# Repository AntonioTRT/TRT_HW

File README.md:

# TRT_HW
# STM32 Modular Audio Platform

Plataforma de hardware abierta en arquitectura Tarjeta Base y Hijas (Carrier & Daughterboard) para audio digital, DSP y control.

## Especificaciones
* MCU: STM32G474RET6 (Cortex-M4 @ 170MHz)
* Aceleradores: FMAC y CORDIC
* Bus B2B: I2S, I2C, SPI, ADC, GPIO
* Alimentación: USB-C / 9V DC
* ECAD: KiCad

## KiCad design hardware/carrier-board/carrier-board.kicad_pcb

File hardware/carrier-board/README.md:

# STM32G474RET6 Carrier Board — Especificación Técnica Oficial

## 1. Descripción General

La **Carrier Board STM32G474** es una plataforma de desarrollo modular de alto rendimiento basada en el microcontrolador ARM Cortex-M4F **STM32G474RET6** (LQFP-64, hasta 170 MHz con FPU y DSP). Diseñada específicamente para fabricación y ensamblaje SMT en **JLCPCB**, utiliza encapsulados estándar fáciles de inspeccionar y soldar (**0805 pasivos, SOT-23, SOD-123 y LQFP-64**).

La tarjeta se interconecta con placas hijas (*daughterboards*) a través del conector Board-to-Board principal **J2 (2x8 pines, numeración estándar 1 a 16)**, integrando buses de comunicación (SPI1, I2C1 con gestión de energía), control de potencia (driver de motor PWM con MOSFET AO3400A) e identificación de hardware digital (HWID de 4 bits).

---

## 2. Especificaciones de Hardware

### 2.1. Alimentación y Regulación
- **Entrada Principal:** +5V nominal vía puerto **USB-C (J6)**. Cuenta con resistencias de pull-down de **5.1 kΩ** en las líneas `CC1` y `CC2` para compatibilidad completa con fuentes y cables USB-C a USB-C (Power Delivery Sink 5V/3A máx).
- **Regulador LDO:** **AMS1117-3.3** en encapsulado SOT-223, entregando un riel de +3.3V regulado (hasta 800 mA de pico / 1 A máx).
- **Filtrado y Desacoplo:**
  - Capacitores cerámicos (MLCC 0805) de **10 µF** en la entrada (+5V) y salida (+3.3V) del regulador.
  - Red de desacoplo distribuida en el MCU: **100 nF** en cada par `VDD`/`VSS` adyacente a los pines, complementados por un capacitor de carga de **10 µF**.
  - **Filtro Analógico:** Perla de ferrita (**FB1**) con capacitor de **100 nF** a masa para las líneas `VDDA` y `VREF+`, aislando el dominio analógico de ruidos digitales.
  - Pin `VBAT` unificado directamente al riel de **+3.3V**.

### 2.2. Reloj, Reset y Depuración
- **Oscilador Principal (HSE):** Cristal de cuarzo pasivo de **8.000 MHz** con capacitores de carga de **22 pF** a GND en `OSC_IN` (PF0) y `OSC_OUT` (PF1).
- **Circuito de Reset (NRST):** Pulsador táctil a GND con resistencia de pull-up de **10 kΩ** a +3.3V y capacitor cerámico de **100 nF** para supresión de rebotes mecánicos y transitorios.
- **Depuración SWD:** Huella estándar **Tag-Connect TC2030-NL / TC2030** que provee:
  - `SWDIO` en **PA13**
  - `SWCLK` en **PA14**
  - `SWO` en **PB3** (Asynchronous Trace)
  - `NRST` para hardware reset por depurador
  - `+3.3V` (VTref) y `GND`

### 2.3. Periféricos e Interfaces On-Board
- **Bus I2C1 con Gestión de Energía:**
  - `PB9` (SDA) y `PB8` (SCL).
  - Resistencias de Pull-Up de **2.2 kΩ** conectadas a un nodo conmutable controlado por el pin **PC15** (`I2C_PU_EN`).
  - Permite desconectar los pull-ups para apagar el bus en modos de bajo consumo (*Sleep/Stop*).
- **Bus SPI1:**
  - `PA5` (SCK), `PA6` (MISO), `PA7` (MOSI), `PB6` (CS).
- **Driver de Motor Low-Side (PWM):**
  - MOSFET canal N **AO3400A** (30V, 5.7A, $R_{DS(on)} < 35\text{ m}\Omega$ a 3.3V $V_{GS}$) en encapsulado SOT-23.
  - Controlado desde el pin **PB4** (Timer 3, Canal 1 / `TIM3_CH1`).
  - Red de compuerta: Resistencia de gate $R_G = 100\ \Omega$ y resistencia pull-down de seguridad $R_{PD} = 10\text{ k}\Omega$ a GND.
  - Protección inductiva: Diodo Schottky Flyback **1N5819HW** (SOD-123) en antiparalelo con la carga + capacitor cerámico de **100 nF** para amortiguación de EMI.
  - Conector de salida de motor **J1** (Paso 2.54 mm): Pin 1 = `+5V`, Pin 2 = `Drain del MOSFET`.
- **LEDs de Diagnóstico:**
  - `LED_PWR` (Verde): Polarizado a +3.3V mediante resistencia de **1 kΩ** ($I_F \approx 1.3\text{ mA}$).
  - `LED_USER` (Azul): Conectado al pin **PA5** (`SPI_SCK`) mediante resistencia de **470 Ω** (emula el `LED_BUILTIN` de Arduino Pin 13).

---

## 3. Conector Board-to-Board (J2 — 2x8 Pines, Numeración Estándar 1 a 16)

El conector principal **J2** utiliza una huella estándar de doble hilera (paso 2.00 mm / 2.54 mm) con numeración numérica consecutiva (Pines 1 al 16), organizada en fila impar (señales SPI / HWID) y fila par (alimentación / I2C / GPIOs):

### 3.1. Tabla de Mapeo Definitiva para J2

| Pin Físico J2 | Fila | Etiqueta de Red | Pin STM32G474 | Funciones Nativas STM32 | Equivalente Arduino | Descripción |
| :---: | :---: | :--- | :---: | :--- | :---: | :--- |
| **Pin 1** | Impar | `SPI_CS / PWM` | **PB6** | TIM4_CH1, TIM16_CH1N, USART1_TX | D10 / PWM | Chip Select SPI o PWM auxiliar |
| **Pin 2** | Par | `GND` | — | Riel de Masa común (0V) | GND | Masa de alimentación |
| **Pin 3** | Impar | `SPI_MOSI / PWM`| **PA7** | SPI1_MOSI, TIM3_CH2, TIM1_CH1N | D11 / PWM | Datos MOSI o salida PWM |
| **Pin 4** | Par | `+5V` | — | Riel de entrada USB VBUS | 5V | Alimentación de potencia principal |
| **Pin 5** | Impar | `SPI_MISO / PWM`| **PA6** | SPI1_MISO, TIM3_CH1, TIM16_CH1, ADC2_IN3 | D12 / PWM | Datos MISO o entrada ADC / PWM |
| **Pin 6** | Par | `TRT_GPIO_1` | **PA1** | TIM2_CH2, USART2_RTS, ADC1_IN2 | D2 / A4 | GPIO / Entrada Analógica / Timer |
| **Pin 7** | Impar | `SPI_SCK / PWM` | **PA5** | SPI1_SCK, TIM2_CH1, ADC2_IN2 | D13 / SCK | Reloj SPI / LED Builtin / PWM |
| **Pin 8** | Par | `+3.3V` | — | Salida del LDO AMS1117-3.3 | 3.3V | Lógica y alimentación de sensores |
| **Pin 9** | Impar | `HWID_0` | **PC0** | ADC1_IN6, ADC2_IN6, LPTIM1_IN1 | A0 | Identificación Hardware Bit 0 (ADC/Digital) |
| **Pin 10**| Par | `TRT_GPIO_2` | **PA4** | DAC1_OUT1, SPI1_NSS, ADC2_IN1 | A5 / DAC | GPIO / Salida Analógica Pura DAC |
| **Pin 11**| Impar | `HWID_1` | **PC1** | ADC1_IN7, ADC2_IN7, LPTIM1_OUT | A1 | Identificación Hardware Bit 1 (ADC/Digital) |
| **Pin 12**| Par | `SDA` | **PB9** | I2C1_SDA, TIM4_CH4, FDCAN1_TX | D14 / SDA | Datos I2C1 (Pull-up conmutable vía PC15) |
| **Pin 13**| Impar | `HWID_2` | **PC2** | ADC1_IN8, ADC2_IN8, LPTIM1_IN2 | A2 | Identificación Hardware Bit 2 (ADC/Digital) |
| **Pin 14**| Par | `SCL` | **PB8** | I2C1_SCL, TIM4_CH3, FDCAN1_RX | D15 / SCL | Reloj I2C1 (Compartido con BOOT0) |
| **Pin 15**| Impar | `HWID_3` | **PC3** | ADC1_IN9, ADC2_IN9, LPTIM1_ETR | A3 | Identificación Hardware Bit 3 (ADC/Digital) |
| **Pin 16**| Par | `TRT_GPIO_3` | **PB0** | TIM1_CH2N, TIM3_CH3, ADC1_IN15 | D3 / PWM | GPIO / PWM auxiliar / ADC |

---

### 3.2. Distribución Física de Pines en el Header (Vista Superior)

```text
               +-------------------+
SPI_CS   (PB6) | [ 1]         [ 2] | GND
SPI_MOSI (PA7) | [ 3]         [ 4] | +5V
SPI_MISO (PA6) | [ 5]         [ 6] | TRT_GPIO_1 (PA1)
SPI_SCK  (PA5) | [ 7]         [ 8] | +3.3V
HWID_0   (PC0) | [ 9]         [10] | TRT_GPIO_2 (PA4)
HWID_1   (PC1) | [11]         [12] | SDA        (PB9)
HWID_2   (PC2) | [13]         [14] | SCL        (PB8)
HWID_3   (PC3) | [15]         [16] | TRT_GPIO_3 (PB0)
               +-------------------+
                    Conector J2
```

---

## 4. Pines Internos y Periféricos Dedicados

| Función | Pin STM32G474 | Características |
| :--- | :--- | :--- |
| **Driver Motor (GATE)** | **PB4** | TIM3_CH1 (PWM Low-Side, MOSFET AO3400A a conector J1) |
| **Habilitador Pull-Up I2C**| **PC15** | Control digital de polarización para resistencias I2C1 (Push-Pull HIGH = ON, High-Z = OFF) |
| **LED Usuario (Azul)** | **PA5** | Compartido con SPI1_SCK (R=470Ω a GND) |
| **USB D-** | **PA11** | USB 2.0 Full Speed Data - |
| **USB D+** | **PA12** | USB 2.0 Full Speed Data + |
| **SWDIO** | **PA13** | Tag-Connect Pin 4 |
| **SWCLK** | **PA14** | Tag-Connect Pin 2 |
| **SWO** | **PB3** | Tag-Connect Pin 6 (Asynchronous SWO Trace) |

---

## 5. Guía de Integración de Firmware

### 5.1. Configuración de Option Bytes para PB8 / BOOT0
El microcontrolador **STM32G474RET6** multiplexa el pin físico 60 entre `PB8` y la señal de selección de arranque `BOOT0`.
- **Problema:** De fábrica, si `nBOOT0_SEL = 1`, en cada reinicio el hardware muestrea el pin PB8. Dado que PB8 está conectado a la línea I2C `SCL` con una resistencia de pull-up, el MCU detectará un nivel alto (`BOOT0 = 1`) y entrará en el bootloader DFU de ST en lugar de ejecutar la memoria Flash.
- **Solución Obligatoria:** Configurar el registro de Option Bytes `FLASH_OPTR`:
  - `nBOOT0_SEL = 0` (Bit 27): El valor de BOOT0 es ignorado desde el pin físico PB8 y se toma del bit de software `nBOOT0`.
  - `nBOOT0 = 1` (Bit 26): En lógica invertida, un valor de `1` equivale a `BOOT0 = 0`, forzando el arranque directo desde la **Flash Principal**.

#### Configuración por Software (HAL / Firmware):
```c
void Configure_Boot_OptionBytes(void) {
    FLASH_OBProgramInitTypeDef obInit = {0};
    
    HAL_FLASH_Unlock();
    HAL_FLASH_OB_Unlock();

    HAL_FLASHEx_OBGetConfig(&obInit);
    
    // Si nBOOT0_SEL está en 1 (muestreo por pin físico PB8), cambiar a software
    if ((obInit.UserConfig & FLASH_OPTR_nBOOT0_SEL) != 0) {
        obInit.OptionType = OPTIONBYTE_USER;
        obInit.UserType   = OB_USER_nBOOT0_SEL | OB_USER_nBOOT0;
        // nBOOT0_SEL = 0 (software), nBOOT0 = 1 (arranque en Flash)
        obInit.UserConfig = OB_nBOOT0_SEL_DISABLE | OB_nBOOT0_SET;
        
        HAL_FLASHEx_OBProgram(&obInit);
        HAL_FLASH_OB_Launch(); // Aplica cambios y reinicia el MCU
    }

    HAL_FLASH_OB_Lock();
    HAL_FLASH_Lock();
}
```

---

### 5.2. Control de Pull-Ups I2C vía PC15 (`I2C_PU_EN`)
Las resistencias de 2.2 kΩ están conectadas al pin **PC15**.

> [!WARNING]
> **Regla de Oro de Firmware para PC15:**
> - Para **ACTIVAR** el bus I2C: Configurar `PC15` como **Salida Push-Pull** en nivel **ALTO** (`GPIO_PIN_SET` = 3.3V).
> - Para **DESACTIVAR** el bus I2C: Configurar `PC15` como **Entrada Flotante (High-Z / No-Pull)**.
> - **NUNCA** configurar `PC15` como salida en nivel **BAJO** (`0V`), ya que esto forzaría a masa las líneas `SDA` y `SCL` mediante 2.2 kΩ, bloqueando la comunicación y consumiendo corriente innecesaria.

#### Implementación HAL:
```c
// Activa las resistencias de pull-up (Bus I2C operativo)
void I2C_Pullups_Enable(void) {
    GPIO_InitTypeDef GPIO_InitStruct = {0};
    __HAL_RCC_GPIOC_CLK_ENABLE();

    GPIO_InitStruct.Pin = GPIO_PIN_15;
    GPIO_InitStruct.Mode = GPIO_MODE_OUTPUT_PP;
    GPIO_InitStruct.Pull = GPIO_NOPULL;
    GPIO_InitStruct.Speed = GPIO_SPEED_FREQ_LOW;
    HAL_GPIO_Init(GPIOC, &GPIO_InitStruct);

    HAL_GPIO_WritePin(GPIOC, GPIO_PIN_15, GPIO_PIN_SET); // Alimenta +3.3V al nodo
}

// Desconecta las resistencias de pull-up (Modo bajo consumo)
void I2C_Pullups_Disable(void) {
    GPIO_InitTypeDef GPIO_InitStruct = {0};
    __HAL_RCC_GPIOC_CLK_ENABLE();

    // Configurar en entrada de alta impedancia (High-Z)
    GPIO_InitStruct.Pin = GPIO_PIN_15;
    GPIO_InitStruct.Mode = GPIO_MODE_INPUT;
    GPIO_InitStruct.Pull = GPIO_NOPULL;
    HAL_GPIO_Init(GPIOC, &GPIO_InitStruct);
}
```

---

### 5.3. Control del Driver de Motor PWM (PB4 / TIM3_CH1)
El MOSFET **AO3400A** es activado directamente por lógica de 3.3V desde `PB4`.

- **Frecuencia óptima recomendada:** 10 kHz a 20 kHz.
- Reloj APB1 (`TIM3CLK`) = 170 MHz.
  - `Prescaler = 16` $\rightarrow$ Frecuencia de conteo = 10 MHz.
  - `Period (ARR) = 999` $\rightarrow$ Frecuencia PWM = 10 kHz ($10\text{ MHz} / 1000$).
  - Resolución del ciclo de trabajo: 0 a 1000 (0% a 100%).

```c
// Iniciar señal PWM
HAL_TIM_PWM_Start(&htim3, TIM_CHANNEL_1);

// Modificar velocidad del motor (0 a 1000)
void Motor_SetSpeed(uint16_t speed) {
    if (speed > 1000) speed = 1000;
    __HAL_TIM_SET_COMPARE(&htim3, TIM_CHANNEL_1, speed);
}
```

---

## 6. Checklist Crítico para el Layout de PCB (JLCPCB)

1. **Ruta de Retorno y Bucles de Potencia del Motor (J1 / AO3400A / D1):**
   - El bucle cerrado formado por `J1 Pin 1 (+5V)` $\rightarrow$ `Motor` $\rightarrow$ `J1 Pin 2` $\rightarrow$ `Diodo 1N5819HW` debe colocarse **lo más compacto posible** para minimizar la radiación EMI.
   - Pistas de potencia entre `J1`, el Drain del MOSFET y el Source a `GND` con un ancho mínimo de **1.2 mm a 1.5 mm** (o polígono de cobre).
   - Colocar el Source del MOSFET directamente a la masa general mediante múltiples vías a plano de masa para evitar ruido por rebote de masa (*ground bounce*).
2. **Ubicación de Condensadores de Desacoplo del MCU:**
   - Cada condensador de **100 nF** debe colocarse inmediatamente adyacente a su respectivo pin `VDD`, conectando primero el pad del capacitor antes de la vía hacia el plano interno.
   - La perla de ferrita `FB1` y su capacitor de 100 nF para `VDDA`/`VREF+` deben ubicarse pegados a los pines 18 y 19.
3. **Oscilador de Cristal HSE de 8 MHz (PF0 / PF1):**
   - Trazar pistas cortas y simétricas entre el cristal y los pines del MCU.
   - Colocar un anillo de guarda de masa (`GND guard ring`) alrededor del cristal y sus capacitores de 22 pF.
   - No rutear señales digitales de alta velocidad (como PWM o SPI) por debajo del oscilador.
4. **Par Diferencial USB (PA11 / PA12):**
   - Impedancia diferencial de **90 Ω**. Ruteo en paralelo con separación constante y longitudes simétricas acopladas.
   - Mantener el plano de masa continuo por debajo sin cortes.

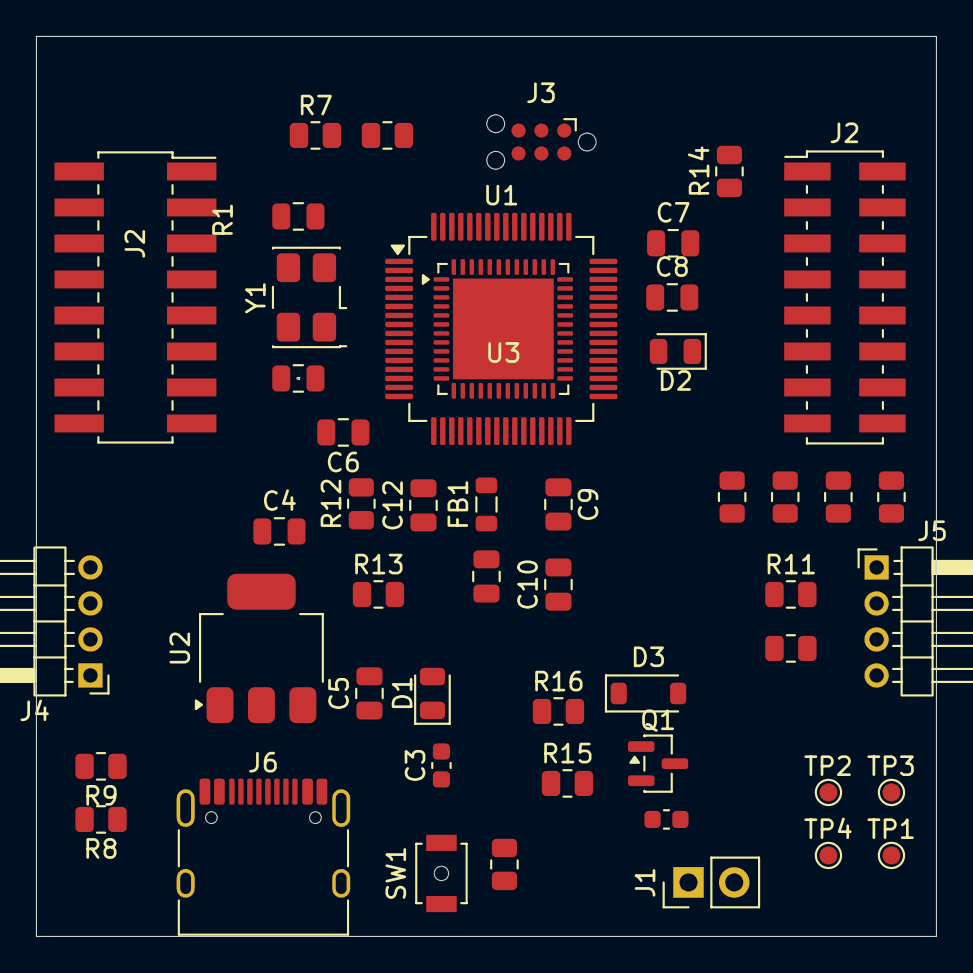
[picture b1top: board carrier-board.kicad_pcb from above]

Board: 4 copper layers, 50.0 x 50.0 mm, 50 parts (0 on the bottom side), 35 nets, no tracks yet.

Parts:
C1, C2: 22pf; C_0805_2012Metric
C3, C13: 100nf; C_0603_1608Metric
C4, C5, C10: 10uF; C_0805_2012Metric
C6, C7, C8, C9, C11, C12: 100nF; C_0805_2012Metric
D1, D2: LED; LED_0805_2012Metric
D3: 1N5819HW; D_SOD-123
FB1: FerriteBead; L_0805_2012Metric
J1: Conn_01x02_Pin; PinHeader_1x02_P2.54mm_Vertical
J2: DIN41612_02x08_AB_EvenPins; PinSocket_2x08_P2.00mm_Vertical_SMD
J2#2: DIN41612_02x08_AB_EvenPins; PinHeader_2x08_P2.00mm_Vertical_SMD
J3: TC2030; Tag-Connect_TC2030-IDC-NL_2x03_P1.27mm_Vertical
J4: Conn_01x04_Socket; PinHeader_1x04_P2.00mm_Horizontal
J5: Conn_01x04_Pin; PinHeader_1x04_P2.00mm_Horizontal
J6: USB_C_Receptacle_USB2.0_16P; USB_C_Receptacle_HRO_TYPE-C-31-M-12
Q1: AO3400A; SOT-23
R1, R2, R3, R4, R5, R6, R7, R12, R15: 10k; R_0805_2012Metric
R8, R9: 5.1k; R_0805_2012Metric
R10, R11: 2.2K; R_0805_2012Metric
R13: 1k; R_0805_2012Metric
R14: 470; R_0805_2012Metric
R16: 100; R_0805_2012Metric
SW1: SW_Push; SW_SPST_B3U-1000P-B
TP1, TP2, TP3, TP4: TestPoint; TestPoint_Pad_D1.0mm
U1: STM32G474RETx; LQFP-64_10x10mm_P0.5mm
U2: AMS1117-3.3; SOT-223-3_TabPin2
U3: STM32F411CEUx; QFN-48-1EP_7x7mm_P0.5mm_EP5.6x5.6mm
Y1: Crystal_GND3; Crystal_SMD_5032-4Pin_5.0x3.2mm

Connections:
+3.3V: C4.1, C6.1, C7.1, C8.1, C9.1, C10.1, FB1.1, J2#2.8, J3.1, R1.1, R7.1, R13.1, TP1.1 (1_1), TP3.1 (1_1), U1.1 (VBAT), U1.16 (VDD), U1.28 (VREF+), U1.32 (VDD), U1.48 (VDD), U1.64 (VDD), U2.2 (VO)
+5V: C5.1, C13.1, D3.1 (K), D3.2 (A), J1.1, J1.2, J2#2.4, J4.1, J5.1, J6.A4 (VBUS), J6.A9 (VBUS), J6.B4 (VBUS), J6.B9 (VBUS), Q1.3 (D), TP2.1 (1_1), U2.3 (VI)
/mcu_core/HWID_0: J2#2.9, R2.1, U1.8 (PC0)
/mcu_core/HWID_1: J2#2.11, R3.1, U1.9 (PC1)
/mcu_core/HWID_2: J2#2.13, R4.1, U1.10 (PC2)
/mcu_core/HWID_3: J2#2.15, R5.1, U1.11 (PC3)
/mcu_core/HWID_A: R6.1, R7.2, U1.12 (PA0)
/mcu_core/I2C_PU_EN: R10.1, R11.1, U1.4 (PC15)
/mcu_core/RESET: C3.1, J3.3, R1.2, SW1.2
/mcu_core/SCL: J2#2.14, J4.3, J5.3, R10.2, U1.61 (PB8)
/mcu_core/SDA: J2#2.12, J4.2, J5.2, R11.2, U1.62 (PB9)
/mcu_core/SPI_CS / PWM: J2#2.1, U1.59 (PB6)
/mcu_core/SPI_MISO / PWM: J2#2.5, U1.20 (PA6)
/mcu_core/SPI_MOSI / PWM: J2#2.3, U1.21 (PA7)
/mcu_core/SPI_SCK / PWM: J2#2.7, R14.1, U1.19 (PA5)
/mcu_core/TRT_GPIO_1: J2#2.6, U1.13 (PA1)
/mcu_core/TRT_GPIO_2: J2#2.10, U1.18 (PA4)
/mcu_core/TRT_GPIO_3: J2#2.16, U1.24 (PB0)
/mcu_core/USB_D+: J6.B6 (D+), U1.46 (PA12)
/mcu_core/USB_D-: J6.B7 (D-), U1.45 (PA11)
/mcu_core/Vm_out: R16.1, U1.57 (PB4)
GND: C1.2, C2.2, C3.2, C4.2, C5.2, C6.2, C7.2, C8.2, C9.2, C10.2, C11.1, C12.1, C13.2, D1.1 (K), D2.1 (K), J2#2.2, J3.5, J4.4, J5.4, J6.A1 (GND), J6.A12 (GND), J6.B1 (GND), J6.B12 (GND), J6.SH (SHIELD), Q1.2 (S), R2.2, R3.2, R4.2, R5.2, R6.2, R8.2, R9.2, R12.1, R15.2, SW1.1, U1.15 (VSS), U1.27 (VSSA), U1.31 (VSS), U1.47 (VSS), U1.63 (VSS), U2.1 (GND), Y1.3
unnamed: D1.2 (A), R13.2
unnamed: D2.2 (A), R14.2
unnamed: J6.A5 (CC1), R8.1
unnamed: J6.B5 (CC2), R9.1
unnamed: Q1.1 (G), R15.1, R16.2
unnamed: J3.2, U1.49 (PA13)
unnamed: J3.4, U1.50 (PA14)
unnamed: J3.6, U1.56 (PB3)
unnamed: R12.2, U1.60 (PB7)
unnamed: C1.1, U1.5 (PF0), Y1.2
unnamed: C2.1, U1.6 (PF1), Y1.1
unnamed: C11.2, C12.2, FB1.2, TP4.1 (1_1), U1.29 (VDDA)
unnamed: U3.23 (VSS), U3.35 (VSS), U3.47 (VSS), U3.49 (VSS)
